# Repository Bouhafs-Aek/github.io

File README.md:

# PCB antennas, done the way a supplier should document them

A working demonstration of integrating printed antennas into an IoT product:
three TI reference antennas built as **exact copies of their published
dimension tables**, each with a program that re-measures the finished file and
fails the build if it has stopped being an exact copy — plus the ground-plane
study, the matching, the simulation models and the bench procedure that turn a
copied shape into a design you can defend.

## [`kicad/kit/`](kicad/kit) — the deliverable: six boards

Three antennas, each built twice. **A PCB antenna is not a component: the
ground plane is part of the antenna**, so which plane you put it on decides
what you measure. One board per antenna cannot answer both questions, so each
gets two.

| | antenna | size | band | note |
|---|---|---|---|---|
| **AN043** | meandered inverted-F | 15 × 6 mm | 2.45 GHz | SWRA117D |
| **DN023** | printed inverted-F | 43 × 20 mm | 868 / 915 / 955 MHz | SWRA228C |
| **DN024** | meandering monopole | 38 × 25 mm | 868 + 2440 MHz | SWRA227E |

* `*_ref` sits on the plane its note publishes — so the measurement
  **validates the build** against TI's own numbers.
* `*_common` sits on a 45 × 60 mm plane shared by all three — so the three
  become **comparable with each other**, which is the question a customer
  actually asks.
* The difference between the two boards of a pair is that antenna's
  **ground-plane sensitivity**, measured rather than asserted.

Everything that is not the antenna or the plane is held constant: 1.6 mm FR4,
the same U.FL launch, the same 2.95 mm 50 Ω line, the same three matching
sites. A checker asserts it, because a kit whose variables leak is not a kit.

**Ready to order:** the three common-plane boards panelise into one
165 × 90 mm, V-scored, 3-up panel — and
[CI](.github/workflows/pcb.yml) builds the gerbers, drill, pick-and-place and
BOM on every push, as a downloadable artifact. Six parts on the whole panel.

## What is actually in here

| | |
|---|---|
| `kicad/kit/` | the six evaluation boards |
| `kicad/dn024/`, `kicad/dn024_ti_form/`, `kicad/swra117d_*` | standalone fabrication projects, including DN024 drawn the way its own Figure 2 draws it |
| `kicad/sim/board/` | two RFsim projects, built so a full-wave run can produce a meaningful answer |
| `kicad/sim/openems/`, `kicad/sim/*.cir` | full-wave and lumped simulation flows that read their geometry out of the board file |
| `kicad/library/` | symbols and footprints, every antenna generated from its published table |
| `kicad/kit/panel_common/` | the three common-plane boards, 3-up and V-scored, with BOM and fabrication export |
| `kicad/tools/` | 35 programs: generators, six checkers, three independent verifiers, two mutation suites, the panel and fabrication tooling |
| `kicad/docs/antenna-integration-checklist.md` | 85 items, every one of them there because getting it wrong here cost a wrong answer |

## The rule the whole repository follows

**Nothing is invented, and everything is checked by something that did not
build it.**

* Each antenna is re-measured out of the written file by a `verify_against_*`
  program that re-derives the note's table by scanline, with no knowledge of
  how the shape was built. It is what found a real bug: a ribbon capped flat
  at its last centre-line point left one stub half a trace short.
* Matching values are copied where a note publishes them (DN024's 3.9 pF) and
  **left unfitted where none does** — the pads are laid out because AN058 asks
  for them, not with numbers made up to fill them.
* Where a note contradicts itself, both readings are written down rather than
  one being chosen in silence. DN023 gives its trim dimension `L6` three
  different values; the board is built at the longest, the two measured ones
  are marked on the silkscreen as a cut scale.
* The checkers are themselves tested: `mutate_*` breaks the boards on purpose
  — **29 faults, 29 caught**.

## Two things worth reading even if you never open KiCad

**[Why a meandered radiator tied to the bottom layer still
radiates](kicad/README.md#two-layers-only-count-as-one-conductor-if-you-stitch-them)** —
and why two unstitched layers are a 140 Ω parallel-plate line that traps the
field instead.

**[The two faults that make a full-wave run
meaningless](kicad/README.md#simulating-it-simboarddn024_monopole_sim)** — a
ground pour stored unfilled, and a 3.9 pF capacitor that a field solver reads
as a 0.40 mm gap, which is −j6100 Ω at 868 MHz. Both look fine on screen, and
both produce a confident, detailed, entirely wrong S11.

Full detail: **[kicad/README.md](kicad/README.md)**.

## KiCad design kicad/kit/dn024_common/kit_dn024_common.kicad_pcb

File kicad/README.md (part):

# TI reference PCB antennas in KiCad — an evaluation kit, with checks and RF simulation

**[`kit/`](#the-evaluation-kit-three-antennas-two-ground-planes) is six boards:
three TI reference antennas, each built twice — once on the ground plane its
note publishes, once on a 45 × 60 mm plane shared by all three.** That is the
deliverable. Everything below it is what the kit is made of.

Three TI reference antennas, each as a complete self-contained KiCad project,
each an exact copy of its application note's dimension table and each with a
checker that fails the build if it stops being one:

* **TI SWRA117D**, a **2.45 GHz printed inverted-F** (left-hand layout) — the
  radiator fed from a 50 Ω SMA port through a pi network carrying a 0 Ω link,
  because the note publishes no matching values and AN058 asks for the pads.
* **TI DN024 / SWRA227E**, a **868 + 2440 MHz meandering monopole** — copper
  on both layers and a pi matching network at the feed, because this note says
  it needs one and gives the values. It comes in **two launches**: an
  edge-mount SMA in `dn024/`, and the note's own vertical through-hole jack
  with the top ground cut away around the feed in `dn024_ti_form/`.

* **TI DN023 / SWRA228C**, a **868 / 915 / 955 MHz printed inverted-F** —
  one layer, no ground beneath it, approximately 50 Ω with nothing fitted, and
  tuned by *trimming* `L6` rather than by matching.

Plus two RFsim projects — the inverted-F drawn the way its Figure 3
draws it — ground on layer 2 only, one via, no connector — and two simulation
flows: a lumped **ngspice** return-loss testbench and a
full-wave **openEMS** model that reads its geometry out of whichever board
file you point it at.

```
kicad/
├── swra117d_2g4_antenna.kicad_pro   project (net classes, design rules)
├── swra117d_2g4_antenna.kicad_sch   schematic: SMA → 50 Ω line → antenna
├── swra117d_2g4_antenna.kicad_pcb   2 layer, 40 × 30 mm, 1.6 mm FR4
├── sym-lib-table / fp-lib-table     point KiCad at the project libraries
├── library/
│   ├── SWRA117D_RF.kicad_sym        antenna, SMA, RF_PORT, GND, PWR_FLAG (+ C, L)
│   ├── TI_DN024.kicad_sym           the second antenna's symbols
│   ├── TI_DN023.kicad_sym           the third antenna's symbols
│   └── TI_DN023.pretty/             TI_DN023_IFA_868.kicad_mod, from Table 1
│   ├── TI_DN024.pretty/
│   │   ├── TI_DN024_Monopole_868_2440.kicad_mod  the radiator, from Table 1
│   │   └── SMA_ThruHole_4Post.kicad_mod          P6, measured off Figure 2
│   └── SWRA117D_RF.pretty/
│       ├── Texas_SWRA117D_2.4GHz_Left.kicad_mod  antenna, as published
│       ├── SWRA117D_2G4_Left_retuned.kicad_mod   antenna, scaled x1.155
│       ├── SMA_EdgeMount_Generic.kicad_mod       50 Ω connector land
│       ├── U_FL_Hirose_U_FL_R_SMT_1_Vertical.kicad_mod  the kit's launch
│       ├── Chip_0402_RF_WideLand.kicad_mod     0402 pitch, 50 Ω-wide pads
│       ├── RF_Port_Land.kicad_mod                the same land, no connector
│       └── Chip_0402_1005Metric_RF.kicad_mod     spare 0402 land
├── kit/                             THE KIT: 6 boards, 3 antennas x 2 planes
│   ├── an043_ref/  an043_common/    2.45 GHz meandered inverted-F
│   ├── dn023_ref/  dn023_common/    868/915 MHz printed inverted-F
│   └── dn024_ref/  dn024_common/    868 + 2440 MHz meandering monopole
├── dn024/                           second antenna: TI DN024 monopole
│   └── dn024_monopole_868_2440.*    868 + 2440 MHz, edge-launch SMA
├── dn024_ti_form/                   the same antenna in the note's own form
│   └── dn024_monopole_ti_form.*     through-hole SMA inboard, ground opening
├── docs/
│   ├── board-drawing.svg            dimensioned drawing, generated from the PCB
│   ├── dn024-board-drawing.svg      the same, for the DN024 board
│   ├── dn024-ti-form-drawing.svg    the same, for the DN024 reference form
│   ├── dn024-sim-board-drawing.svg  the same, for the DN024 RFsim model
│   ├── sim-board-drawing.svg        the same, for the simulation board
│   └── antenna-integration-checklist.md   design review list for any project
├── sim/
│   ├── antenna_swra117d.lib         lumped antenna model (ngspice subckt)
│   ├── s11_antenna.cir              S11 / VSWR / Zin at the connector
│   ├── board/swra117d_2g4_sim.*     RFsim project: Figure 3, ground on layer 2
│   ├── board/dn024_monopole_sim.*   RFsim project: DN024, Z62 shorted, no pours
│   └── openems/swra117d_openems.py  full-wave S11, impedance, directivity
└── tools/                           generators, checkers, line + scaling calculators
```

Open `swra117d_2g4_antenna.kicad_pro` in KiCad, then press **B** in the PCB
editor to fill the ground zones (they are stored unfilled).

## KiCad version

Every file is written in the KiCad 9.x s-expression format
(`kicad_sym` 20241209, `kicad_sch` 20250114, `kicad_pcb` 20241229). KiCad 10
reads those directly and rewrites them in its own format the first time you
save — that is the normal upgrade path and nothing is lost.

## The signal path

```
J1  SMA edge launch  ──  2.95 mm wide 50 Ω microstrip, 23.5 mm  ──  AE1 pin 1 (FEED)
    shell ── GND         one straight run, no corner              AE1 pin 2 (GND) ── GND
```

The connector sits on the bottom edge directly below the antenna's feed pad
and faces it, so the feed is a single vertical run. That is as short as an
edge-launch connector can be here: the antenna owns the top edge, its ground
pin blocks any approach from the right, and the SMA needs 12.95 mm of board edge
with all of it on the ground plane — which only the bottom edge offers.

Two nets on the `RF_50R` net class (2.95 mm, 0.3 mm clearance): `RF_IN` from
the connector to the series position, `ANT_FEED` from there to the radiator.
Nothing *corrects* the antenna — SWRA117D says it is already a 50 Ω design and
publishes no values — but the pi network is laid out and linked with a 0 Ω, so
there is somewhere to compensate an enclosure later. See
[The pi network](#the-pi-network-pads-and-a-0-Ω-link) for what to do if the assembled
product lands off band.

`#FLG01` (a `PWR_FLAG`) sits on the ground net — this board is entirely
passive, so without it ERC reports the ground pins as power inputs that
nothing drives.

## The antenna is a DC short

Worth knowing before any simulator or multimeter surprises you: **pad 1 and
pad 2 are connected by the radiator**. The arm is one continuous piece of
copper that lands on the feed pad at one end and on the ground pad at the
other — that is the shorting strap, the "F" in inverted-F. The port sees
0 Ω to ground at DC.

The footprint does not make this obvious, which is why `check_project.py`
asserts it. The polygon looks like it has an isolation ring around pad 2, but
that 22-vertex ring is 0.147–0.152 mm in radius: it is the 0.15 mm **drill
barrel** punched out of the copper, not a gap. Probe anywhere else on pad 2's
land and you are on the radiator:

```
pad 1 centre                       inside radiator copper = True
pad 2 centre (in the drill hole)   inside radiator copper = False
pad 2 copper, +0.2 mm in y         inside radiator copper = True
pad 2 copper, ±0.3 mm in x         inside radiator copper = True
```

**This is why a circuit-level RF extraction of this board reports VSWR → ∞.**
A tool that turns the layout into transmission lines and lumped connectivity
has no radiation mechanism, so the only thing it can see at the port is a
shorted stub: |Γ| = 1. Radiation resistance — the ~50 Ω that makes the
antenna work — exists only in a solver that lets power leave the board. So a
huge VSWR from a quasi-static or TL extractor is that model being used outside
its domain, not a fault in the feed line. Use openEMS (or any full-wave
solver) for the antenna, and the lumped model in `sim/` for the match.

If you want to check the *feed line* separately from the antenna, that is
worth doing and it is easy: terminate the line into 50 Ω instead of the
radiator — delete AE1 temporarily, or in RFsim put port 2 at the antenna feed
pad and look at S21 and the port impedances.

## The symbols

`library/SWRA117D_RF.kicad_sym` is the project's only symbol library. The
schematic places four of its symbols — the antenna, `Conn_Coaxial_SMA`, `GND`
and `PWR_FLAG`; the RFsim project places `RF_PORT` in place of the connector;
and `C` and `L` are kept spare for a matching network.

They live in-project on purpose: a schematic embeds a copy of every symbol it
places, and KiCad raises `lib_symbol_mismatch` whenever that copy differs from
the library it names — which it will for any stock symbol whose definition
moves between library releases. Resolving them here makes the project
self-contained and ERC-clean on any install. If you would rather use the stock
symbols, swap the `lib_id`s and run *Tools → Update Symbols from Library* —
but check `Conn_Coaxial_SMA` afterwards, because stock
`Connector:Conn_Coaxial` puts pin 1 on the other side and the wire will need
redrawing.

The antenna symbol is `ANT_SWRA117D_2G4_Left`:

| pin | name | type | goes to |
|-----|------|------|---------|
| 1 | FEED | passive | 50 Ω feed line |
| 2 | GND  | passive | ground plane edge, right at the feed |

It is drawn over a ground bar, carries the TI application-note URL as its
datasheet, is pre-linked to the antenna footprint, filters the footprint
chooser to `Texas_SWRA117D*`, and carries the `Sim.*` fields that point
KiCad's built-in ngspice at `sim/antenna_swra117d.lib`.

Pin 2 matters: this is an *inverted-F*, not a monopole. The footprint's second
pad is the ground/short pin and it has to sit on the edge of the ground plane,
which is what the board below does.

## Simulating this board: four settings that decide whether the answer means anything

An RFsim run of this board reported resonance at 2.83 GHz, and the board
carried a x1.155 scaled radiator for one commit because of it. **That number
was not usable, and the scaling has been reverted.** The layout plot from the
run shows why: the only copper on the board is the antenna, the feed line and
the connector pads. The ground pours are absent, and the dialog was set to
RFsim's FR-4 preset rather than this board's stackup. Two large errors pulling
in opposite directions.

Before trusting any result from this board, check all four:

| setting | must be | why |
|---|---|---|
| **copper zones** | **filled** — press **B** in the PCB editor before exporting | An inverted-F radiates *against its ground plane*; the plane is half the antenna. With the pours unfilled there is no plane at all, only the connector's pads, and the 41 stitching vias connect to nothing. This is not a small error — it is a different antenna. |
| **substrate** | **1.6 mm, εr 4.5** | This is the fabricated stackup, and it happens to be RFsim's FR-4 preset, so this setting is usually right by accident. Check it anyway: the field-plot caption names the mid-plane, and it should read 0.80 mm. On 0.8 mm the 2.95 mm line would be **32 Ω**, not 50. |
| **domain margin** | **≥ λ/4 at the lowest frequency in the sweep** — 31 mm from 2.45 GHz, but **37.5 mm** from a sweep that starts at 2 GHz | At the 4 mm default the absorbing boundary sits inside the antenna's near field — λ/31 away — so it truncates the fields that make the antenna an antenna. The number follows the sweep, not the design frequency: starting at 2.3 GHz instead of 2.0 asks for 32.6 mm rather than 37.5 and cuts the domain volume by a third. `sim/openems/swra117d_openems.py` uses 30 mm, which suits its own 1.45–3.45 GHz excitation. |
| **port** | attached to the feed line: **Coplanar (CPW)** on the fabrication board, **Microstrip (MSL)** on the RFsim project, which has no connector pads beside the line | The dialog showed *Port 1 [No Track]*, *Feed: No Line*, Lumped, width 3.114 mm. The width was never the problem: 3.11 mm is the 50 Ω width for this stackup with copper thickness ignored, and the board's 2.95 mm is the same width with it. *No Track* and *No Line* were the problem — a lumped port that is not attached to anything excites nothing. |

The stackup leaves a usable fingerprint in RFsim's own guess:
`tools/line_impedance.py` gives 50 Ω at **3.03 mm** on 1.6 mm / εr 4.5 with
zero-thickness copper and **2.97 mm** with 35 µm of it. RFsim guessed
3.114 mm, so RFsim was reading 1.6 mm all along — which, once the board owner
confirmed 1.6 mm, turned out to be right.

### Retuning, once a valid run exists

Uniform in-plane scaling is the retune whose physics needs no model of the
meander: scale every dimension *and every gap* by k and each current path and
coupling distance scales with it, so the resonance moves as 1/k. It also
carries the feed tap and the short along with it, so the input impedance is
preserved — lengthening one arm by hand would fix the frequency and break the
50 Ω. It is first order only (the substrate thickness does not scale), so
expect to iterate.

```sh
python3 tools/scale_footprint.py \
    library/SWRA117D_RF.pretty/Texas_SWRA117D_2.4GHz_Left.kicad_mod \
    library/SWRA117D_RF.pretty/SWRA117D_2G4_Left_retuned.kicad_mod \
    --scale <f_measured / 2.45> --name SWRA117D_2G4_Left_retuned
# then set ANT_SCALE and ANT_FOOTPRINT in tools/gen_project.py
python3 tools/gen_project.py
```

### Run log

Five full-wave runs so far. The frequency a run reports is only as good as
the setup behind it, so the setup is recorded with it:

| run | board | ground plane | substrate | domain | resonance |
|---|---|---|---|---|---|
| 1 | fabrication | **absent** (pours unfilled) | 1.6 mm (preset) | **4 mm** | 2.83 GHz |
| 2 | fabrication | present | 1.6 mm (mid-plane caption read 0.80 mm) | **4 mm** | 2.02 GHz |
| 3 | fabrication | to confirm | to confirm | to confirm | 2.82 GHz, VSWR 1.2 |
| 4 | fabrication | present | 1.6 mm (mid-plane caption again read 0.80 mm) | **4 mm**, bright field on the boundary | 2.65 GHz |
| 5 | **RFsim project** (Figure 3) | present, layer 2 | 1.6 mm | to confirm | **2.575 GHz, −38.5 dB** |

Run 5 is the first with a model that is not obviously wrong: no connector, no
top pour, ground on one layer, MSL port on a pad with reference copper under
it. It is also the first that looks like an antenna rather than like a setup
artefact — one clean resonance, smooth either side, no ripple against the
boundary.

The substrate column is no longer bolded as a fault: the board owner has since
confirmed 1.6 mm, so the simulator's preset was right and this project's
0.8 mm assumption was the error. What remains wrong in every one of these runs
is the 4 mm domain, and in run 1 the missing ground plane.

Runs 1–4 span **2.02 – 2.83 GHz: 810 MHz, or 33% of the target frequency**, on
a board whose copper did not meaningfully change. No geometry moved by 33%.
That spread was the measurement, not the antenna. Runs 1 and 3 agree, and that
agreement means nothing on its own: run 1 had no ground plane at all, which is
a different antenna, and it landed on the same number as a run that had one.

#### What run 5 says

Read off the plot, so ±0.01 GHz and ±1 dB:

| | |
|---|---|
| resonance | **2.575 GHz**, 5.1% above 2.45 |
| depth | **−38.5 dB**, VSWR **1.02** |
| −10 dB band | ≈ 2.48 – 2.68 GHz, **200 MHz**, 7.8% (TI quotes bandwidth at VSWR 2.0 = −9.5 dB, marginally wider) |
| at 2.400 GHz | ≈ −5.5 dB, VSWR 3.3 |
| at 2.4835 GHz | ≈ −11 dB, VSWR 1.8 |

Two separate results, and it is worth keeping them apart.

**The match is excellent and that is a real finding.** −38.5 dB is not
something a mis-set port produces by accident: it says the feed tap sits in
the right place relative to the short, which is Table 1's D5 = 1.40 mm doing
its job. The bandwidth is 200 MHz where the ISM band needs 83 MHz, so there is
more than twice the bandwidth required — the antenna does not need widening,
only centring.

**The frequency is 5.1% high**, which as it stands leaves 2.400 GHz at VSWR
3.3: the band is not covered at the low end. Resonance high means the radiator
is electrically short, and uniform scaling by k = 2.575 / 2.45 = **1.051**
would centre it while preserving the feed-to-short ratio, so the match should
survive.

#### Before scaling anything

5.1% is small enough to be the model rather than the antenna, and that
distinction decides whether to touch copper at all:

* **εr is a guess.** FR4 is quoted 4.2–4.8 between vendors and batches. The
  antenna has no ground under it so it sits mostly in air and is less sensitive
  than the feed line is, but not insensitive — and 4.5 is a nominal value, not
  a measurement of this laminate.
* **The model has no solder mask.** The real board has ~25 µm of εr ≈ 3.5
  resin over the radiator, which loads it and pulls resonance *down* by roughly
  a percent. That is a third of this error, in the right direction, and it is
  absent from the model by construction.
* **Etch tolerance** moves a 0.5 mm strip by a few percent of its width.

So a 5% error is inside the envelope of the model's own inputs. Scaling the
copper to cancel it would be fitting the geometry to an uncertainty.

**And there is a reason not to aim at 2.45 GHz in free space at all.** AN058's
measurements of a handheld PCB antenna show plastic encapsulation pulling the
resonance *down*, and a hand holding the encapsulated device pulling it down
further still — the effect only ever goes one way. An antenna centred on the
band on the bench is an antenna sitting below the band once it is in its case.
So the free-space target is not the band centre; it is the band centre plus
whatever the enclosure takes away, which is a number you get by measuring your
enclosure. Run 5 being 5% high is, on its own, not obviously the wrong place
to be.

AN058 does confirm the *direction*, for when there is something to correct:
*"if the resonance frequency is too low, the antenna should be made shorter.
If the resonance frequency is too high, the antenna length should be
increased."* Uniform scaling by k > 1 lengthens every path at once, which is
what `tools/scale_footprint.py` does.

**The gate**, unchanged in principle and now down to two items for run 5:

1. ~~copper pours filled~~ — the ground is a filled zone in the exported
   geometry, or there would be no resonance at all.
2. ~~substrate 1.6 mm, εr 4.5~~ — confirmed by the board owner.
3. **domain margin ≥ 37.5 mm.** λ/4 at the *lowest* frequency in the sweep,
   and this sweep starts at 2 GHz, not 2.45 — so 31 mm is not enough here,
   37.5 mm is. Check the field plot extends that far past the copper and is
   dark at the boundary. Starting the sweep at 2.3 GHz instead would drop the
   requirement to 32.6 mm and shrink the domain volume by a third.
4. **Run it twice.** A converged model gives the same answer twice, and this
   one has not yet been asked to.

Confirm those two and `k = 1.051` is a two-line change:

```sh
python3 tools/scale_footprint.py     library/SWRA117D_RF.pretty/Texas_SWRA117D_2.4GHz_Left.kicad_mod     library/SWRA117D_RF.pretty/SWRA117D_2G4_Left_retuned.kicad_mod     --scale 1.051 --name SWRA117D_2G4_Left_retuned
# then ANT_SCALE = 1.051 and ANT_FOOTPRINT = "SWRA117D_2G4_Left_retuned"
```

The scaled radiator is 15.13 × 5.68 mm of copper against 14.40 × 5.40 mm, and
its keep-out box reaches y = 60.77 mm against a board edge at 60.00, so it
still fits with 0.77 mm to spare. `SWRA117D_2G4_Left_retuned.kicad_mod` is in
the library at ×1.155 from the discredited run 3 and has not been regenerated:
**the board carries the published geometry**, and it stays that way until a
confirmed run says otherwise.

The honest alternative to scaling is to build one board and put a VNA on it.
A 5% model error against an unmeasured laminate is exactly the situation the
application note's own remedy addresses — *"To compensate for a
thicker/thinner PCB the antenna could be made slightly shorter/longer"* — and
it is cheaper to trim after a measurement than to guess before one.

### Verified against the application note

SWRA117D (AN043) states the antenna as a dimension table, and states why it
matters: *"Small changes of the antenna dimensions may have large impact on
the performance. Therefore it is strongly recommended to make an exact copy of
the reference design to achieve optimum performance."*

`tools/verify_against_swra117d.py` measures the footprint's geometry out of
the polygon and compares it with Table 1. **All 14 dimensions match within
11 µm** — L1–L6, W1, W2 and D1–D6, including both repeats of the meander:

```
L1  3.94   3.940   open-end leg, under the top strip
L2  2.70   2.700   meander top strips (second instance 2.700)
L3  5.00   5.000   first top strip, ground leg to first finger
L4  2.64   2.640   meander finger depth
L5  2.00   2.000   meander bottom links (second instance 2.000)
L6  4.90   4.900   feed and ground legs
W1  0.90   0.900   ground (shorting) leg width
W2  0.50   0.500   trace width everywhere else
D1  0.50   0.500   clearance beyond the ground leg
D2  0.30   0.300   clearance above the top strip
D3  0.30   0.300   clearance beyond the open end
D4  0.50   0.500   feed/ground pad height at the plane edge
D5  1.40   1.400   gap, feed leg to ground leg
D6  1.70   1.700   gap, feed leg to first meander finger
```

`check_project.py` runs this on whichever antenna footprint the board
actually carries, so a scaled or redrawn radiator fails the build rather than
passing quietly. Putting the ×1.155 variant back reports:

```
FAIL board: SWRA117D_2G4_Left_retuned is not an exact copy of SWRA117D
     Table 1 - 14 dimension(s) differ, worst L3 by +775 um
```

Two things fall out of the table that the drawing alone does not tell you.
The keep-out box is not arbitrary: D1, D2 and D3 are the note's own
clearances, and D4 is the pad height at the plane edge — which is why the
ground plane edge is read from that box rather than typed in. And the note's
"15.2 × 5.7 mm" envelope is the copper (14.4 × 5.4 mm) plus exactly those
clearances.

### The stackup: 1.6 mm, confirmed by the board owner

SWRA117D does not give the stackup. It says *"It is also recommended to use
the same thickness and type of PCB material as used in the reference design.
Information about the PCB can be found in a separate readme file included in
the reference design"* — a readme we do not have. What it does give is the
remedy: *"To compensate for a thicker/thinner PCB the antenna could be made
slightly shorter/longer."*

**The board is 1.6 mm FR4.** That is the fabricated reality, so the design
follows it, and the simulator was right all along — it was this project's
0.8 mm assumption that was wrong. Everything downstream is derived, so the
change was one constant:

| | 0.8 mm (was) | 1.6 mm (is) |
|---|---|---|
| 50 Ω microstrip | 1.50 mm | **2.95 mm** (50.2 Ω) |
| SMA signal pad | 1.5 mm | **2.95 mm**, footprint generated to match |
| coplanar gap at the launch | 0.8 mm → 48.8 Ω | **2.0 mm → 49.8 Ω** |
| top pour keep-away | 1.0 mm | **2.0 mm** |
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
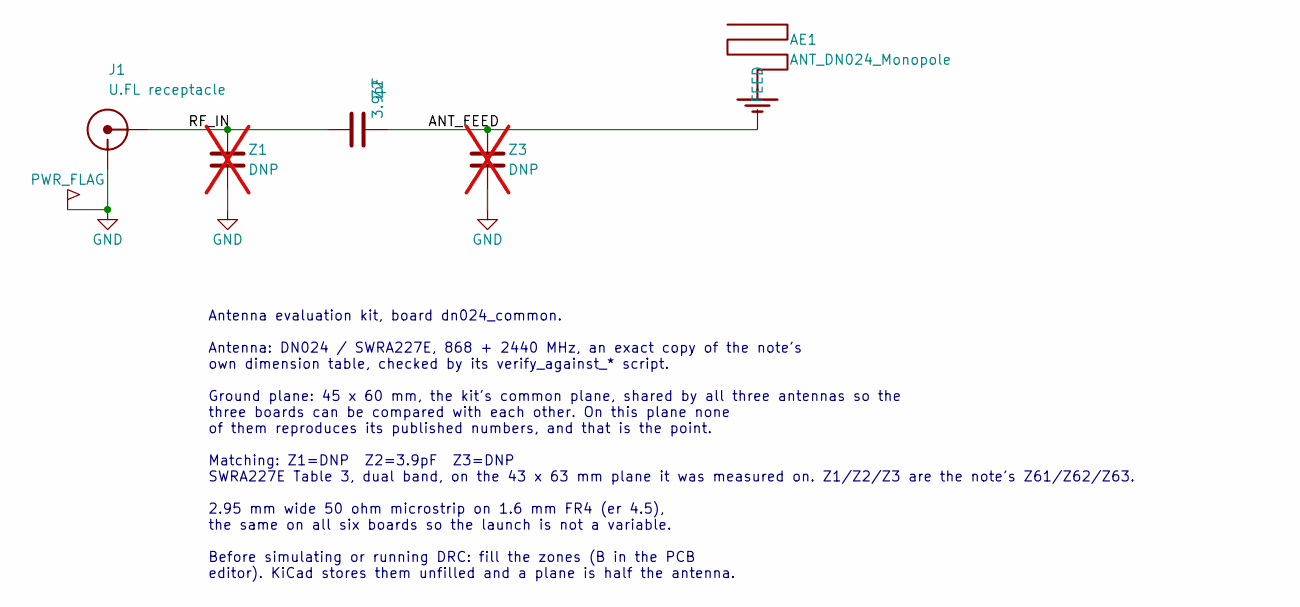
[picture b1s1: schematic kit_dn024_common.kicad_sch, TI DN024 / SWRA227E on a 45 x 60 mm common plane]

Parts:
AE1: ANT_DN024_Monopole; TI_DN024_Monopole_868_2440
J1: U.FL receptacle; U_FL_Hirose_U_FL_R_SMT_1_Vertical
Z1, Z3: DNP; Chip_0402_1005Metric_RF; not fitted
Z2: 3.9pF; Chip_0402_1005Metric_RF

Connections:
ANT_FEED: AE1.1 (ANT_FEED), Z2.2 (ANT_FEED), Z3.1 (ANT_FEED)
GND: J1.2 (GND), Z1.2 (GND), Z3.2 (GND)
RF_IN: J1.1 (SIGNAL), Z1.1 (RF_IN), Z2.1 (RF_IN)

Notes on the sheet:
Antenna evaluation kit, board dn024_common. Antenna: DN024 / SWRA227E, 868 + 2440 MHz, an exact copy of the note's own dimension table, checked by its verify_against_* script. Ground plane: 45 x 60 mm, the kit's common plane, shared by all three antennas so the three boards can be compared with eac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

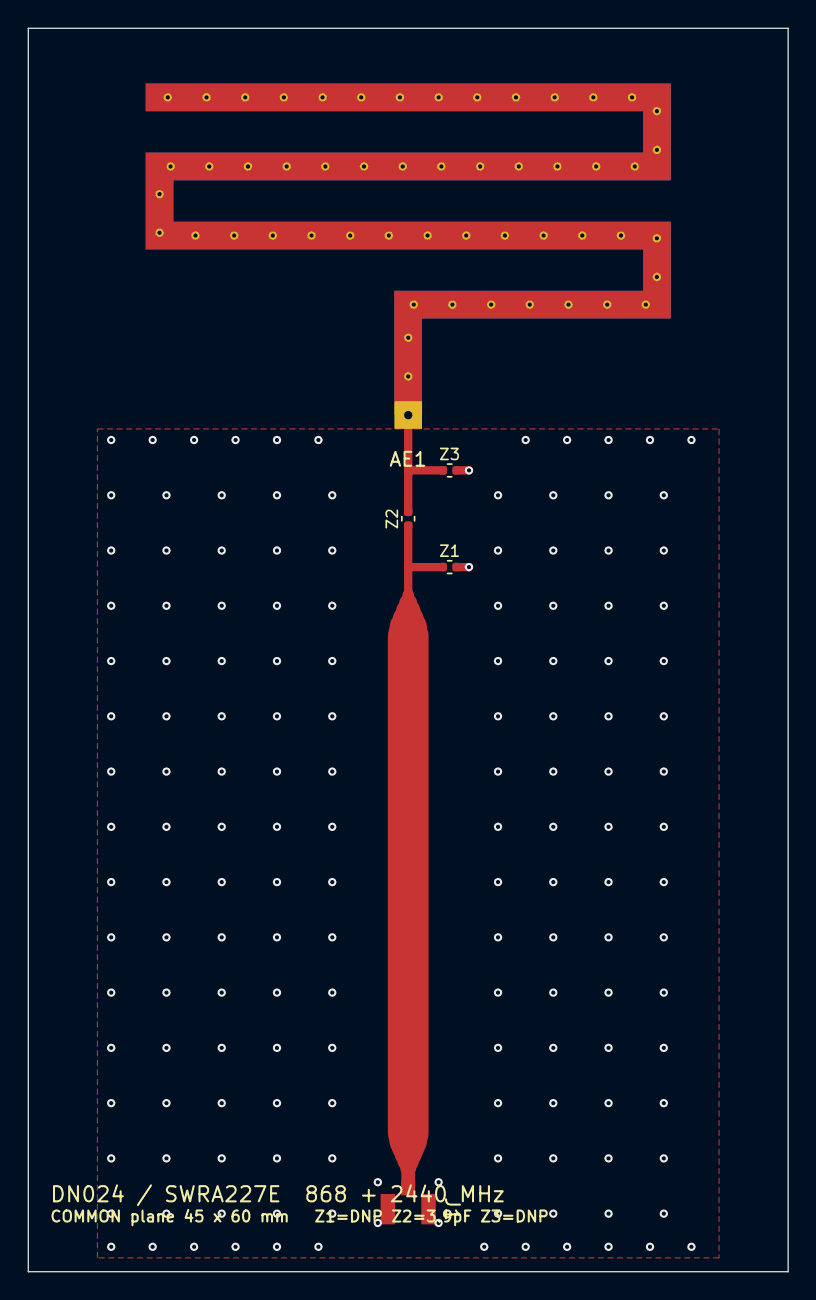
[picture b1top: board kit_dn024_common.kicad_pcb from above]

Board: 2 copper layers, 55.0 x 90.0 mm, 5 parts (0 on the bottom side), 3 nets.

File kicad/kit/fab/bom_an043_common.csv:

reference,qty,value,footprint,fitted,manufacturer_part,note
J1,1,U.FL receptacle,U_FL_Hirose_U_FL_R_SMT_1_Vertical,yes,Hirose U.FL-R-SMT-1(10),"mates with a U.FL to SMA pigtail, not supplied on the board"
Z2,1,0R,Chip_0402_1005Metric_RF,yes,any 0402 0 ohm link,no matching values are published for this antenna; the link makes the site a through
Z1 Z3,2,DNP,Chip_0402_1005Metric_RF,no,,"land laid out, nothing fitted - for compensating an enclosure later (AN058, and SWRA228C section 3)"

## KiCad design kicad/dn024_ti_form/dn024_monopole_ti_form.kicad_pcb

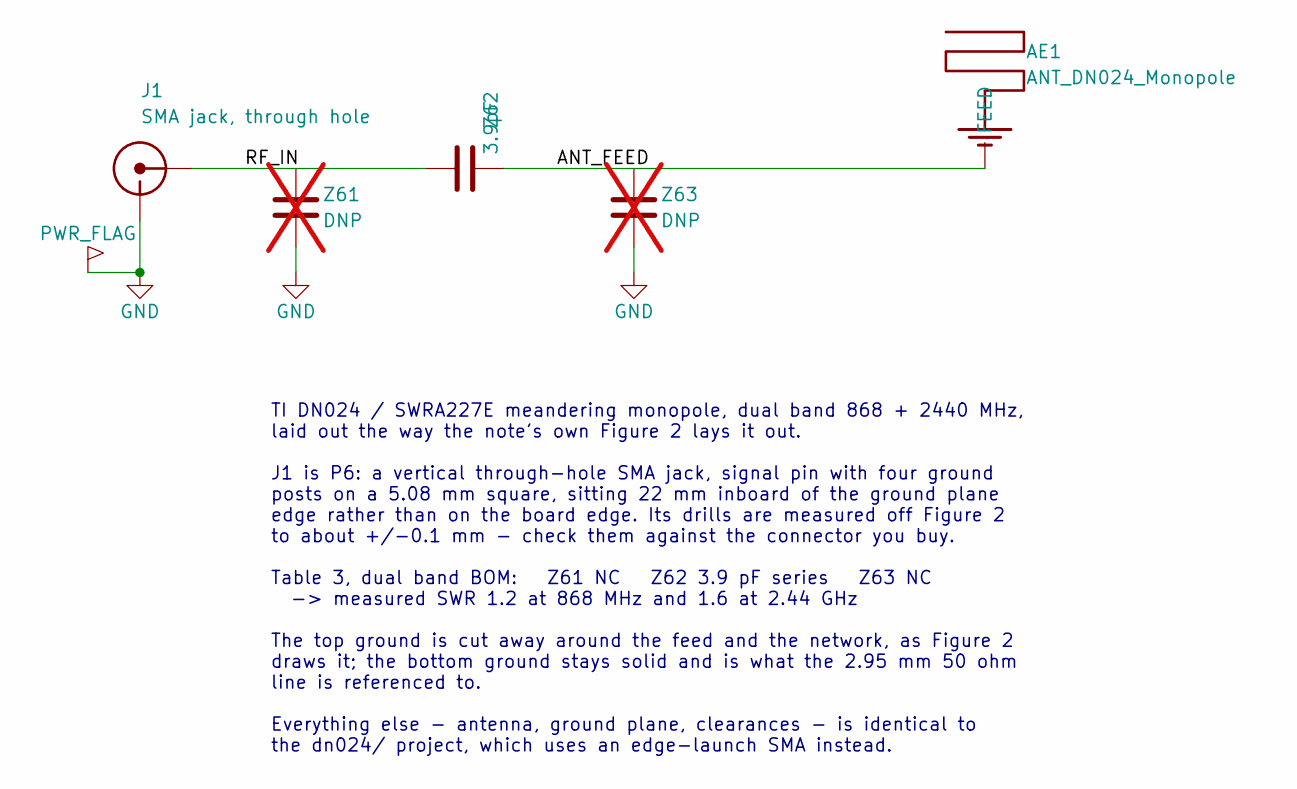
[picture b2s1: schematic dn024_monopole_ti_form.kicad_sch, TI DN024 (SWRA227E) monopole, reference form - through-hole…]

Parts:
AE1: ANT_DN024_Monopole; TI_DN024_Monopole_868_2440
J1: SMA jack, through hole; SMA_ThruHole_4Post
Z61, Z63: DNP; Chip_0402_1005Metric_RF; not fitted
Z62: 3.9pF; Chip_0402_1005Metric_RF

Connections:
ANT_FEED: AE1.1 (ANT_FEED), Z62.2 (ANT_FEED), Z63.1 (ANT_FEED)
GND: J1.2 (GND), Z61.2 (GND), Z63.2 (GND)
RF_IN: J1.1 (RF_IN), Z61.1 (RF_IN), Z62.1 (RF_IN)

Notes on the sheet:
TI DN024 / SWRA227E meandering monopole, dual band 868 + 2440 MHz, laid out the way the note's own Figure 2 lays it out. J1 is P6: a vertical through-hole SMA jack, signal pin with four ground posts on a 5.08 mm square, sitting 22 mm inboard of the ground plane edge rather than on the board edge. I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

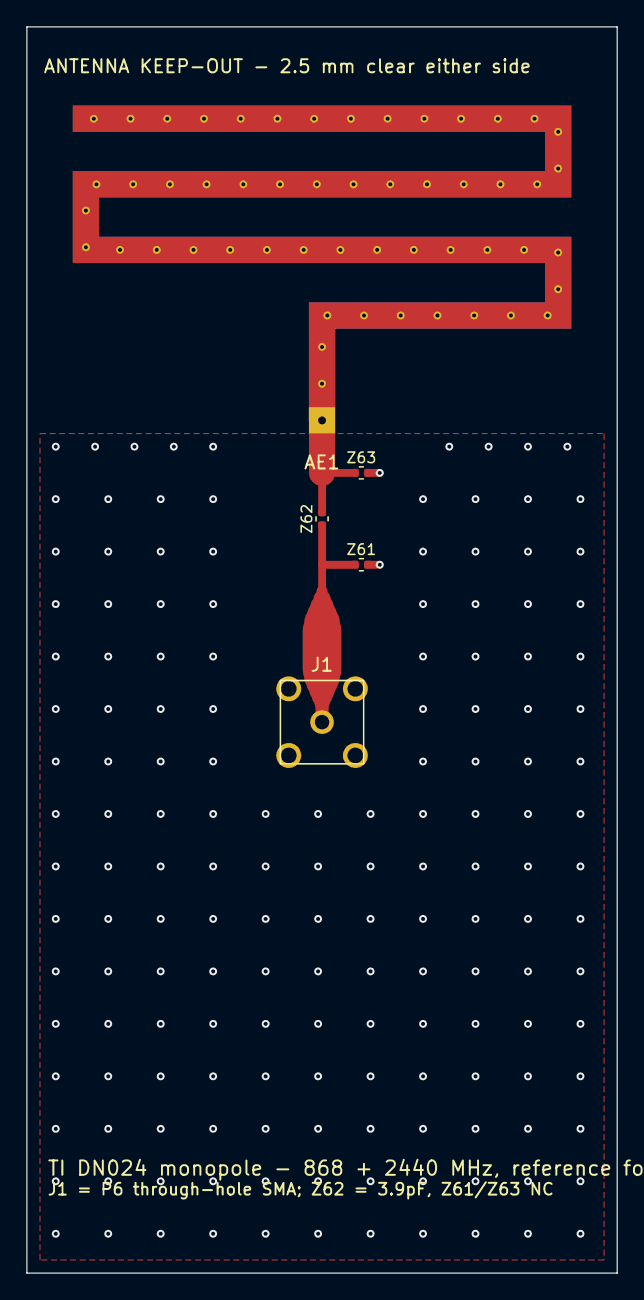
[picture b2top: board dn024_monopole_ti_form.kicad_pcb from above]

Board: 2 copper layers, 45.0 x 95.0 mm, 5 parts (0 on the bottom side), 3 nets.

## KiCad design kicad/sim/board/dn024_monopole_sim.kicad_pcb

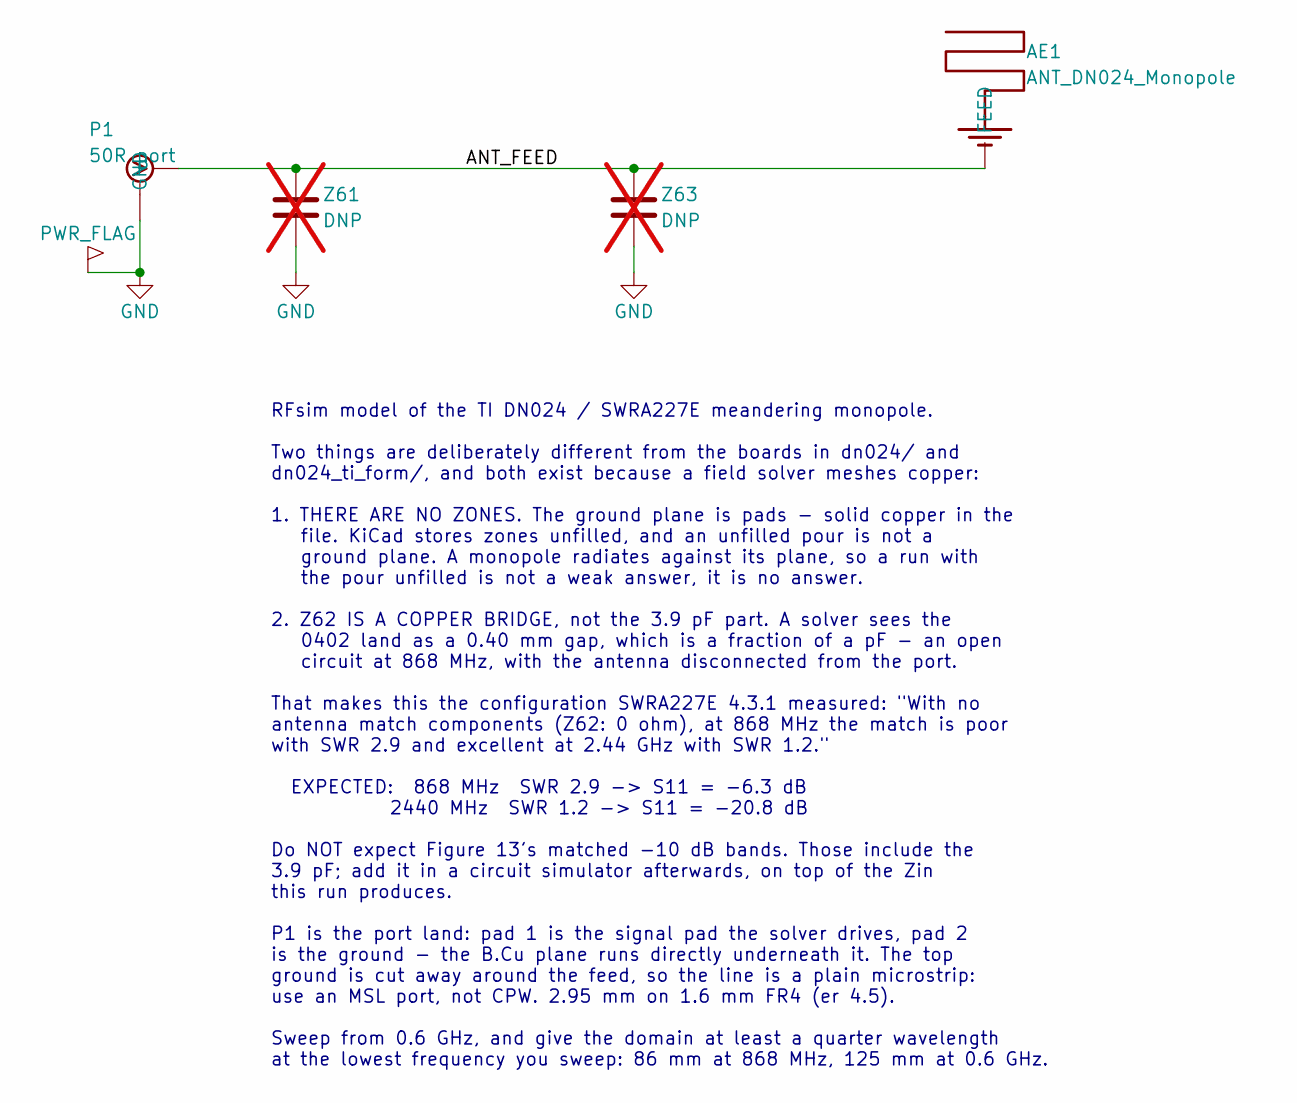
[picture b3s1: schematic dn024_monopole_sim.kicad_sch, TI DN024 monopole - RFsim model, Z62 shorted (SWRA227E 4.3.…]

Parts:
AE1: ANT_DN024_Monopole; TI_DN024_Monopole_868_2440
P1: 50R port; DN024_Sim_Plane_Port
Z61, Z63: DNP; Chip_0402_1005Metric_RF; not fitted

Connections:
ANT_FEED: AE1.1 (ANT_FEED), P1.1 (ANT_FEED), Z61.1 (ANT_FEED), Z63.1 (ANT_FEED)
GND: P1.2 (GND), Z61.2 (GND), Z63.2 (GND)

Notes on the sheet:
RFsim model of the TI DN024 / SWRA227E meandering monopole. Two things are deliberately different from the boards in dn024/ and dn024_ti_form/, and both exist because a field solver meshes copper: 1. THERE ARE NO ZONES. The ground plane is pads - solid copper in the file. KiCad stores zones unfille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

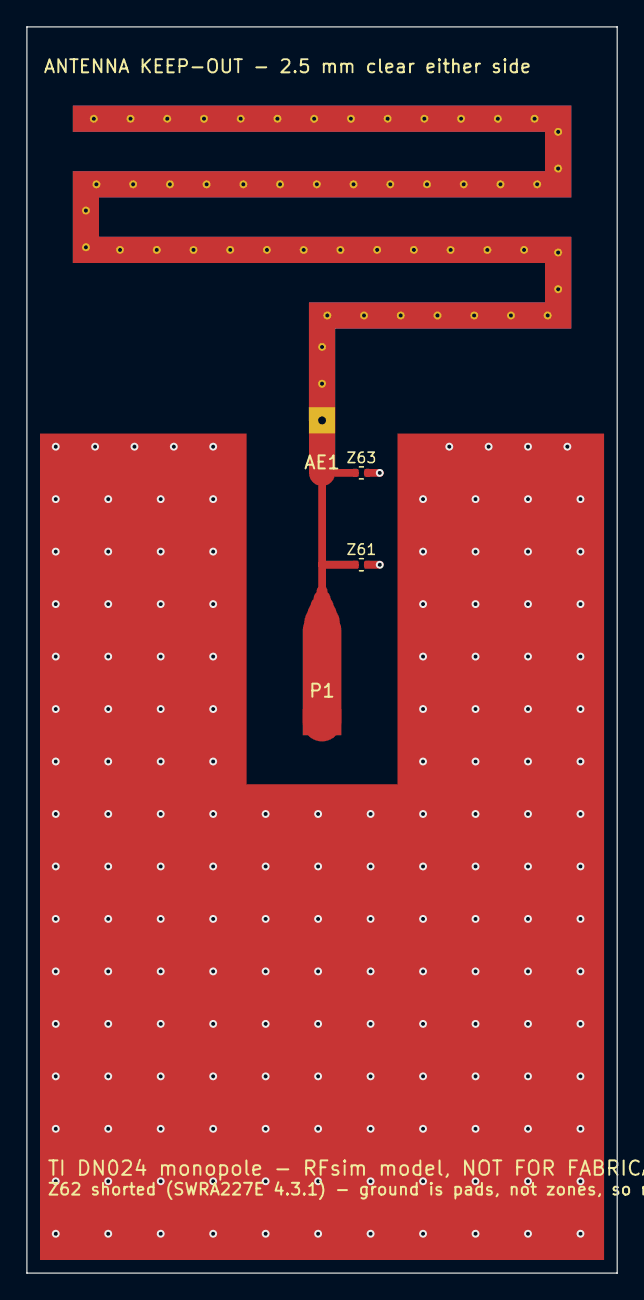
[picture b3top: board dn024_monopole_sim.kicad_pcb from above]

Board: 2 copper layers, 45.0 x 95.0 mm, 4 parts (0 on the bottom side), 2 nets.

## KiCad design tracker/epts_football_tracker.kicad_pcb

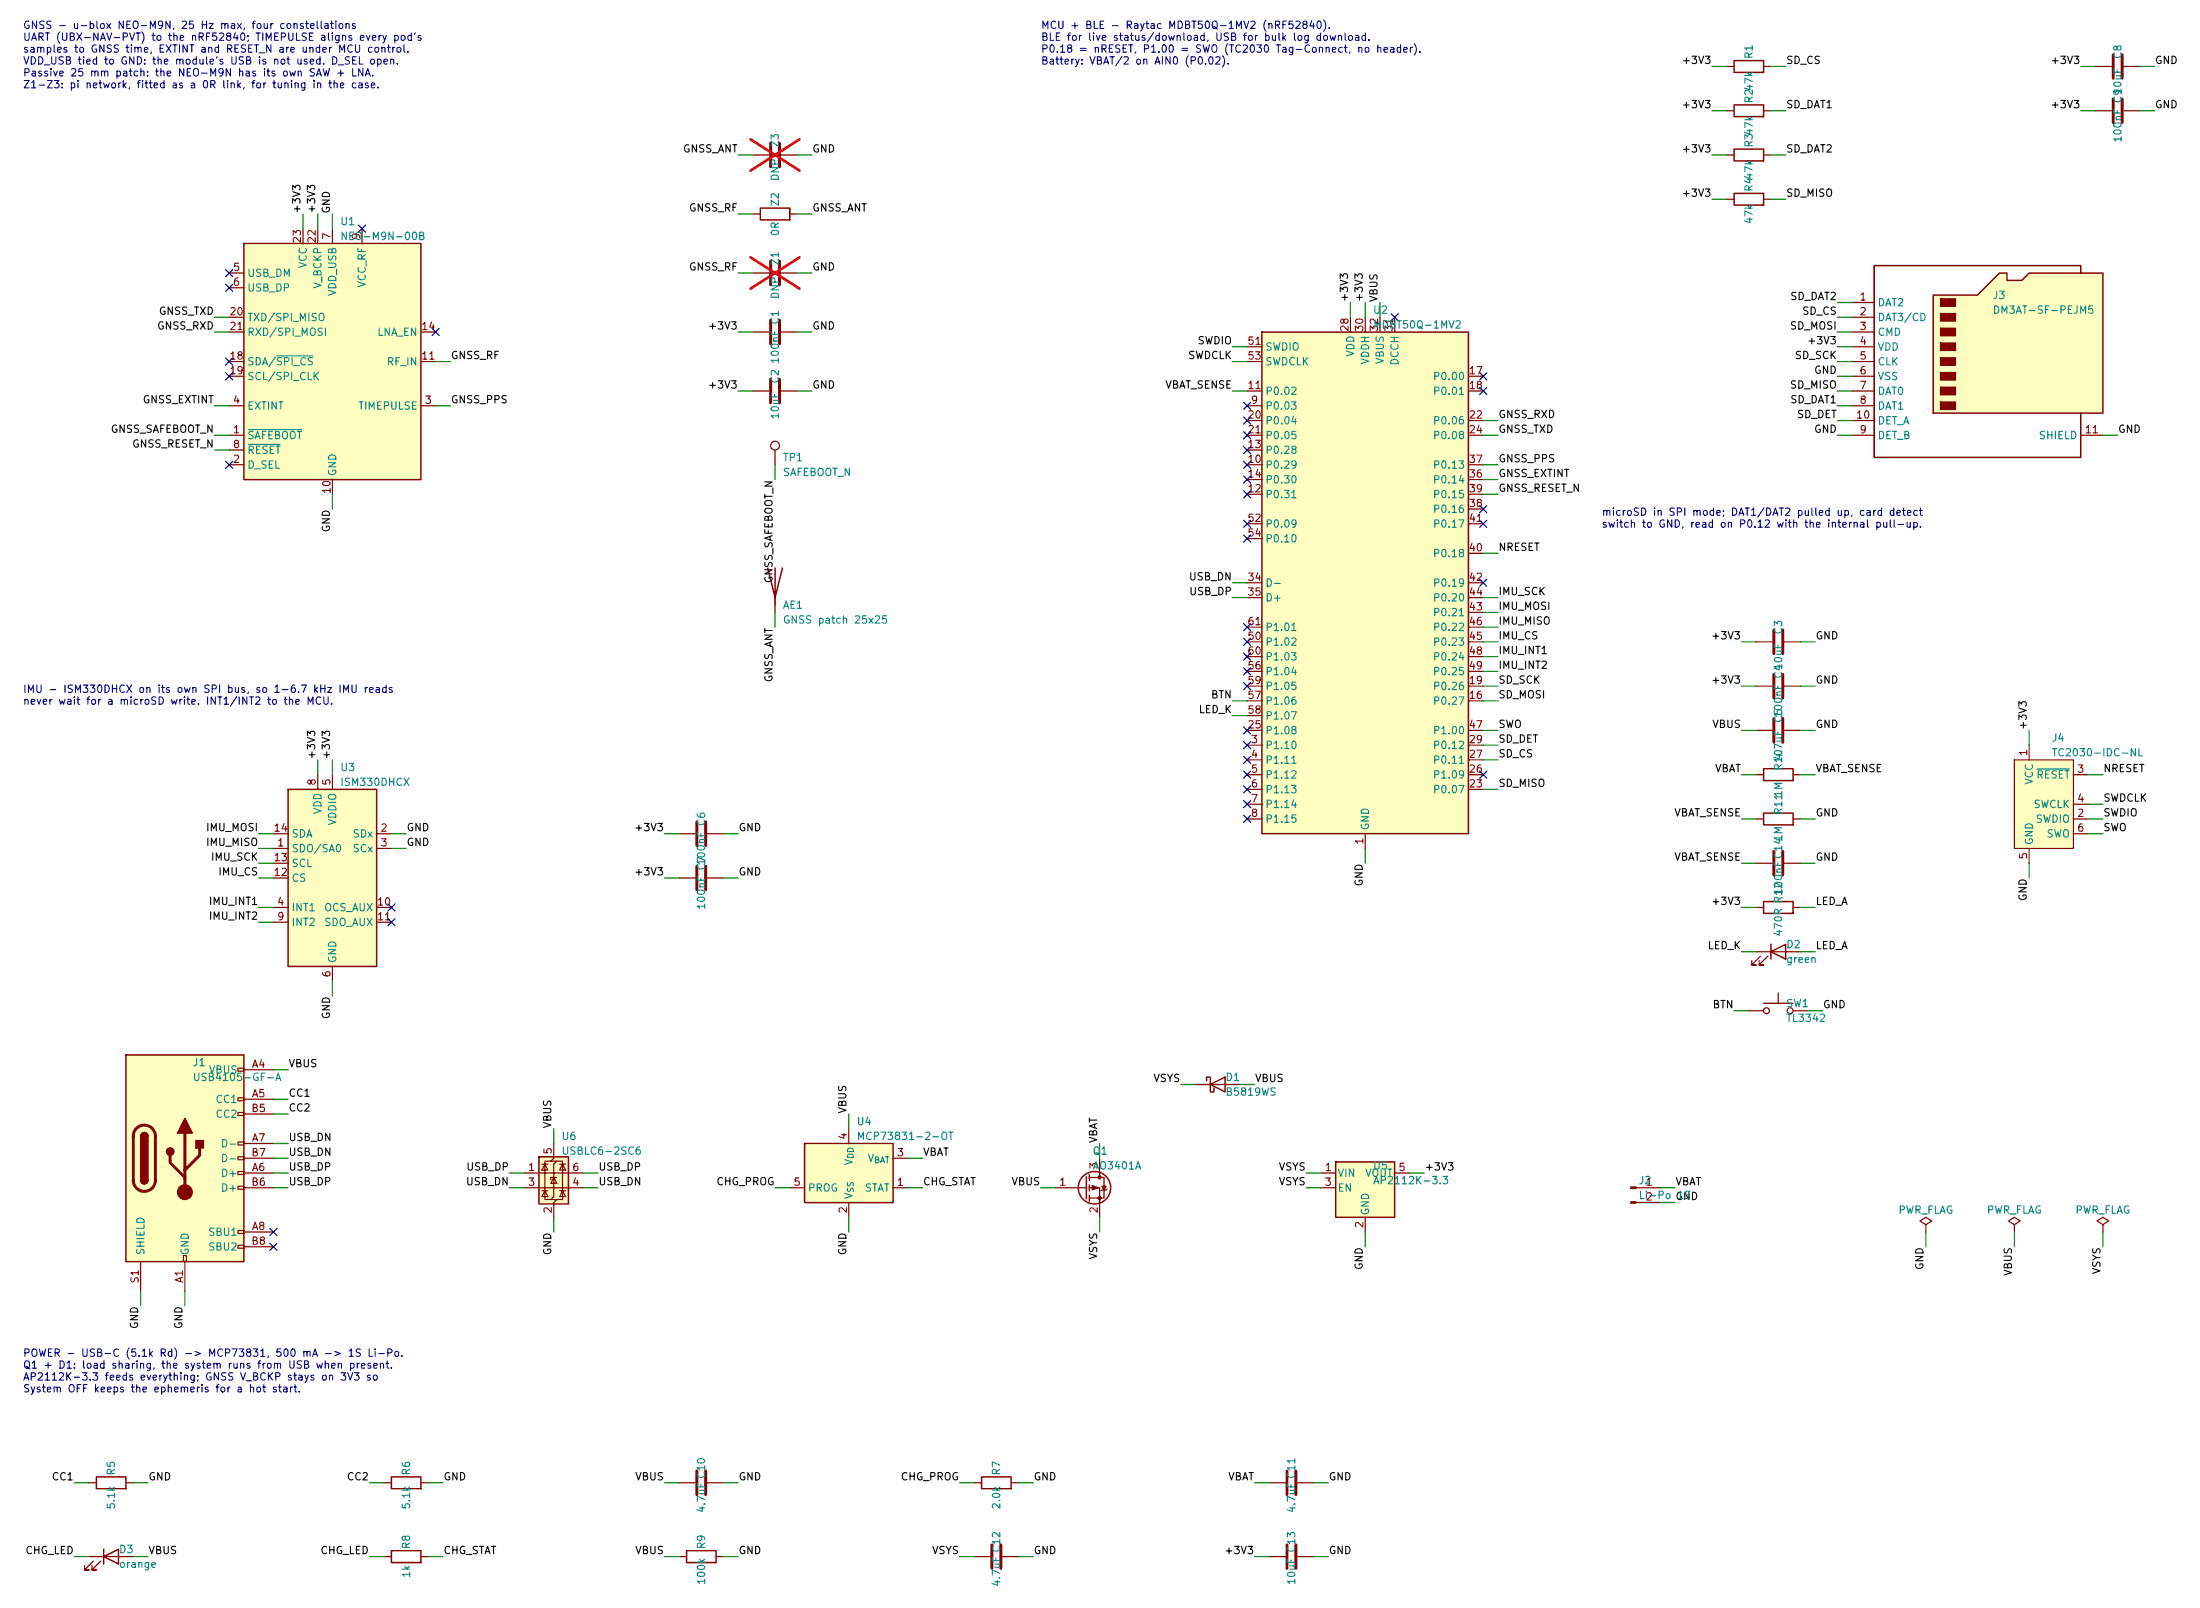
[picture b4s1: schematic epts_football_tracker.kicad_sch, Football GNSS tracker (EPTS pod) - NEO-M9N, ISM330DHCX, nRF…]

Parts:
AE1: GNSS patch 25x25; GNSS_Patch_25x25mm_SingleFeed
C1, C4, C6, C7, C9, C14: 100nF; C_0402_1005Metric
C2, C3, C8, C13: 10uF; C_0805_2012Metric
C5, C10, C11, C12: 4.7uF; C_0603_1608Metric
D1: B5819WS; D_SOD-323
D2: green; LED_0603_1608Metric
D3: orange; LED_0603_1608Metric
J1: USB4105-GF-A; USB_C_Receptacle_GCT_USB4105-xx-A_16P_TopMnt_Horizontal
J2: Li-Po 1S; JST_PH_S2B-PH-SM4-TB_1x02-1MP_P2.00mm_Horizontal
J3: DM3AT-SF-PEJM5; microSD_HC_Hirose_DM3AT-SF-PEJM5
J4: TC2030-IDC-NL; Tag-Connect_TC2030-IDC-NL_2x03_P1.27mm_Vertical
Q1: AO3401A; SOT-23
R1, R2, R3, R4: 47k; R_0402_1005Metric
R5, R6: 5.1k; R_0402_1005Metric
R7: 2.0k; R_0402_1005Metric
R8: 1k; R_0402_1005Metric
R9: 100k; R_0402_1005Metric
R10, R11: 1M; R_0402_1005Metric
R12: 470R; R_0402_1005Metric
SW1: TL3342; SW_SPST_TL3342
TP1: SAFEBOOT_N; TestPoint_Pad_D1.0mm
U1: NEO-M9N-00B; ublox_NEO
U2: MDBT50Q-1MV2; Raytac_MDBT50Q
U3: ISM330DHCX; LGA-14_3x2.5mm_P0.5mm_LayoutBorder3x4y
U4: MCP73831-2-OT; SOT-23-5
U5: AP2112K-3.3; SOT-23-5
U6: USBLC6-2SC6; SOT-23-6
Z1, Z3: DNP; C_0402_1005Metric; not fitted
Z2: 0R; R_0402_1005Metric

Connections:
+3V3: C1.1 (+3V3), C2.1 (+3V3), C3.1 (+3V3), C4.1 (+3V3), C6.1 (+3V3), C7.1 (+3V3), C8.1 (+3V3), C9.1 (+3V3), C13.1 (+3V3), J3.4 (+3V3), J4.1 (+3V3), R1.1 (+3V3), R2.1 (+3V3), R3.1 (+3V3), R4.1 (+3V3), R12.1 (+3V3), U1.22 (+3V3), U1.23 (+3V3), U2.28 (+3V3), U2.30 (+3V3), U3.5 (+3V3), U3.8 (+3V3), U5.5 (+3V3)
BTN: SW1.1 (BTN), U2.57 (BTN)
CC1: J1.A5 (CC1), R5.1 (CC1)
CC2: J1.B5 (CC2), R6.1 (CC2)
CHG_LED: D3.1 (CHG_LED), R8.1 (CHG_LED)
CHG_PROG: R7.1 (CHG_PROG), U4.5 (CHG_PROG)
CHG_STAT: R8.2 (CHG_STAT), U4.1 (CHG_STAT)
GND: C1.2 (GND), C2.2 (GND), C3.2 (GND), C4.2 (GND), C5.2 (GND), C6.2 (GND), C7.2 (GND), C8.2 (GND), C9.2 (GND), C10.2 (GND), C11.2 (GND), C12.2 (GND), C13.2 (GND), C14.2 (GND), J1.A1 (GND), J1.A12 (GND), J1.B1 (GND), J1.B12 (GND), J1.S1 (GND), J2.2 (GND), J3.6 (GND), J3.9 (GND), J3.11 (GND), J4.5 (GND), R5.2 (GND), R6.2 (GND), R7.2 (GND), R9.2 (GND), R11.2 (GND), SW1.2 (GND), U1.7 (GND), U1.10 (GND), U1.12 (GND), U1.13 (GND), U1.24 (GND), U2.1 (GND), U2.2 (GND), U2.15 (GND), U2.33 (GND), U2.55 (GND), U3.2 (GND), U3.3 (GND), U3.6 (GND), U3.7 (GND), U4.2 (GND), U5.2 (GND), U6.2 (GND), Z1.2 (GND), Z3.2 (GND)
GNSS_ANT: AE1.1 (GNSS_ANT), Z2.2 (GNSS_ANT), Z3.1 (GNSS_ANT)
GNSS_EXTINT: U1.4 (GNSS_EXTINT), U2.36 (GNSS_EXTINT)
GNSS_PPS: U1.3 (GNSS_PPS), U2.37 (GNSS_PPS)
GNSS_RESET_N: U1.8 (GNSS_RESET_N), U2.39 (GNSS_RESET_N)
GNSS_RF: U1.11 (GNSS_RF), Z1.1 (GNSS_RF), Z2.1 (GNSS_RF)
GNSS_RXD: U1.21 (GNSS_RXD), U2.22 (GNSS_RXD)
GNSS_SAFEBOOT_N: TP1.1 (GNSS_SAFEBOOT_N), U1.1 (GNSS_SAFEBOOT_N)
GNSS_TXD: U1.20 (GNSS_TXD), U2.24 (GNSS_TXD)
IMU_CS: U2.45 (IMU_CS), U3.12 (IMU_CS)
IMU_INT1: U2.48 (IMU_INT1), U3.4 (IMU_INT1)
IMU_INT2: U2.49 (IMU_INT2), U3.9 (IMU_INT2)
IMU_MISO: U2.46 (IMU_MISO), U3.1 (IMU_MISO)
IMU_MOSI: U2.43 (IMU_MOSI), U3.14 (IMU_MOSI)
IMU_SCK: U2.44 (IMU_SCK), U3.13 (IMU_SCK)
LED_A: D2.2 (LED_A), R12.2 (LED_A)
LED_K: D2.1 (LED_K), U2.58 (LED_K)
NRESET: J4.3 (NRESET), U2.40 (NRESET)
SD_CS: J3.2 (SD_CS), R1.2 (SD_CS), U2.27 (SD_CS)
SD_DAT1: J3.8 (SD_DAT1), R2.2 (SD_DAT1)
SD_DAT2: J3.1 (SD_DAT2), R3.2 (SD_DAT2)
SD_DET: J3.10 (SD_DET), U2.29 (SD_DET)
SD_MISO: J3.7 (SD_MISO), R4.2 (SD_MISO), U2.23 (SD_MISO)
SD_MOSI: J3.3 (SD_MOSI), U2.16 (SD_MOSI)
SD_SCK: J3.5 (SD_SCK), U2.19 (SD_SCK)
SWDCLK: J4.4 (SWDCLK), U2.53 (SWDCLK)
SWDIO: J4.2 (SWDIO), U2.51 (SWDIO)
SWO: J4.6 (SWO), U2.47 (SWO)
USB_DN: J1.A7 (USB_DN), J1.B7 (USB_DN), U2.34 (USB_DN), U6.3 (USB_DN), U6.4 (USB_DN)
USB_DP: J1.A6 (USB_DP), J1.B6 (USB_DP), U2.35 (USB_DP), U6.1 (USB_DP), U6.6 (USB_DP)
VBAT: C11.1 (VBAT), J2.1 (VBAT), Q1.3 (VBAT), R10.1 (VBAT), U4.3 (VBAT)
VBAT_SENSE: C14.1 (VBAT_SENSE), R10.2 (VBAT_SENSE), R11.1 (VBAT_SENSE), U2.11 (VBAT_SENSE)
VBUS: C5.1 (VBUS), C10.1 (VBUS), D1.2 (VBUS), D3.2 (VBUS), J1.A4 (VBUS), J1.A9 (VBUS), J1.B4 (VBUS), J1.B9 (VBUS), Q1.1 (VBUS), R9.1 (VBUS), U2.32 (VBUS), U4.4 (VBUS), U6.5 (VBUS)
VSYS: C12.1 (VSYS), D1.1 (VSYS), Q1.2 (VSYS), U5.1 (VSYS), U5.3 (VSYS)

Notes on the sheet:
GNSS - u-blox NEO-M9N, 25 Hz max, four constellations UART (UBX-NAV-PVT) to the nRF52840; TIMEPULSE aligns every pod's samples to GNSS time, EXTINT and RESET_N are under MCU control. VDD_USB tied to GND: the module's USB is not used. D_SEL open. Passive 25 mm patch: the NEO-M9N has its own SAW + LN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
IMU - ISM330DHCX on its own SPI bus, so 1-6.7 kHz IMU reads never wait for a microSD write. INT1/INT2 to the MCU.
MCU + BLE - Raytac MDBT50Q-1MV2 (nRF52840). BLE for live status/download, USB for bulk log download. P0.18 = nRESET, P1.00 = SWO (TC2030 Tag-Connect, no header). Battery: VBAT/2 on AIN0 (P0.02).
microSD in SPI mode; DAT1/DAT2 pulled up, card detect switch to GND, read on P0.12 with the internal pull-up.
POWER - USB-C (5.1k Rd) -> MCP73831, 500 mA -> 1S Li-Po. Q1 + D1: load sharing, the system runs from USB when present. AP2112K-3.3 feeds everything; GNSS V_BCKP stays on 3V3 so System OFF keeps the ephemeris for a hot start.

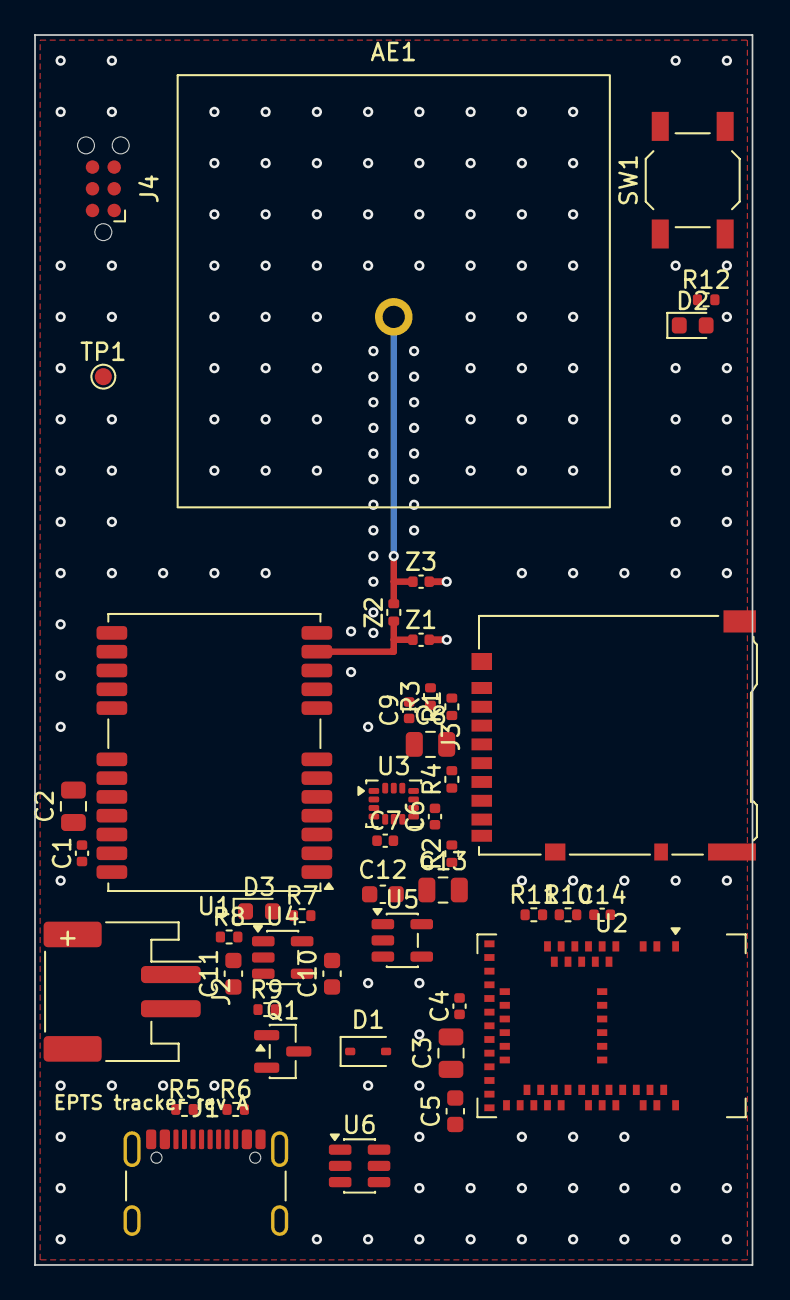
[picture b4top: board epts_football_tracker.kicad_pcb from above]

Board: 4 copper layers, 42.0 x 72.0 mm, 46 parts (0 on the bottom side), 41 nets.
